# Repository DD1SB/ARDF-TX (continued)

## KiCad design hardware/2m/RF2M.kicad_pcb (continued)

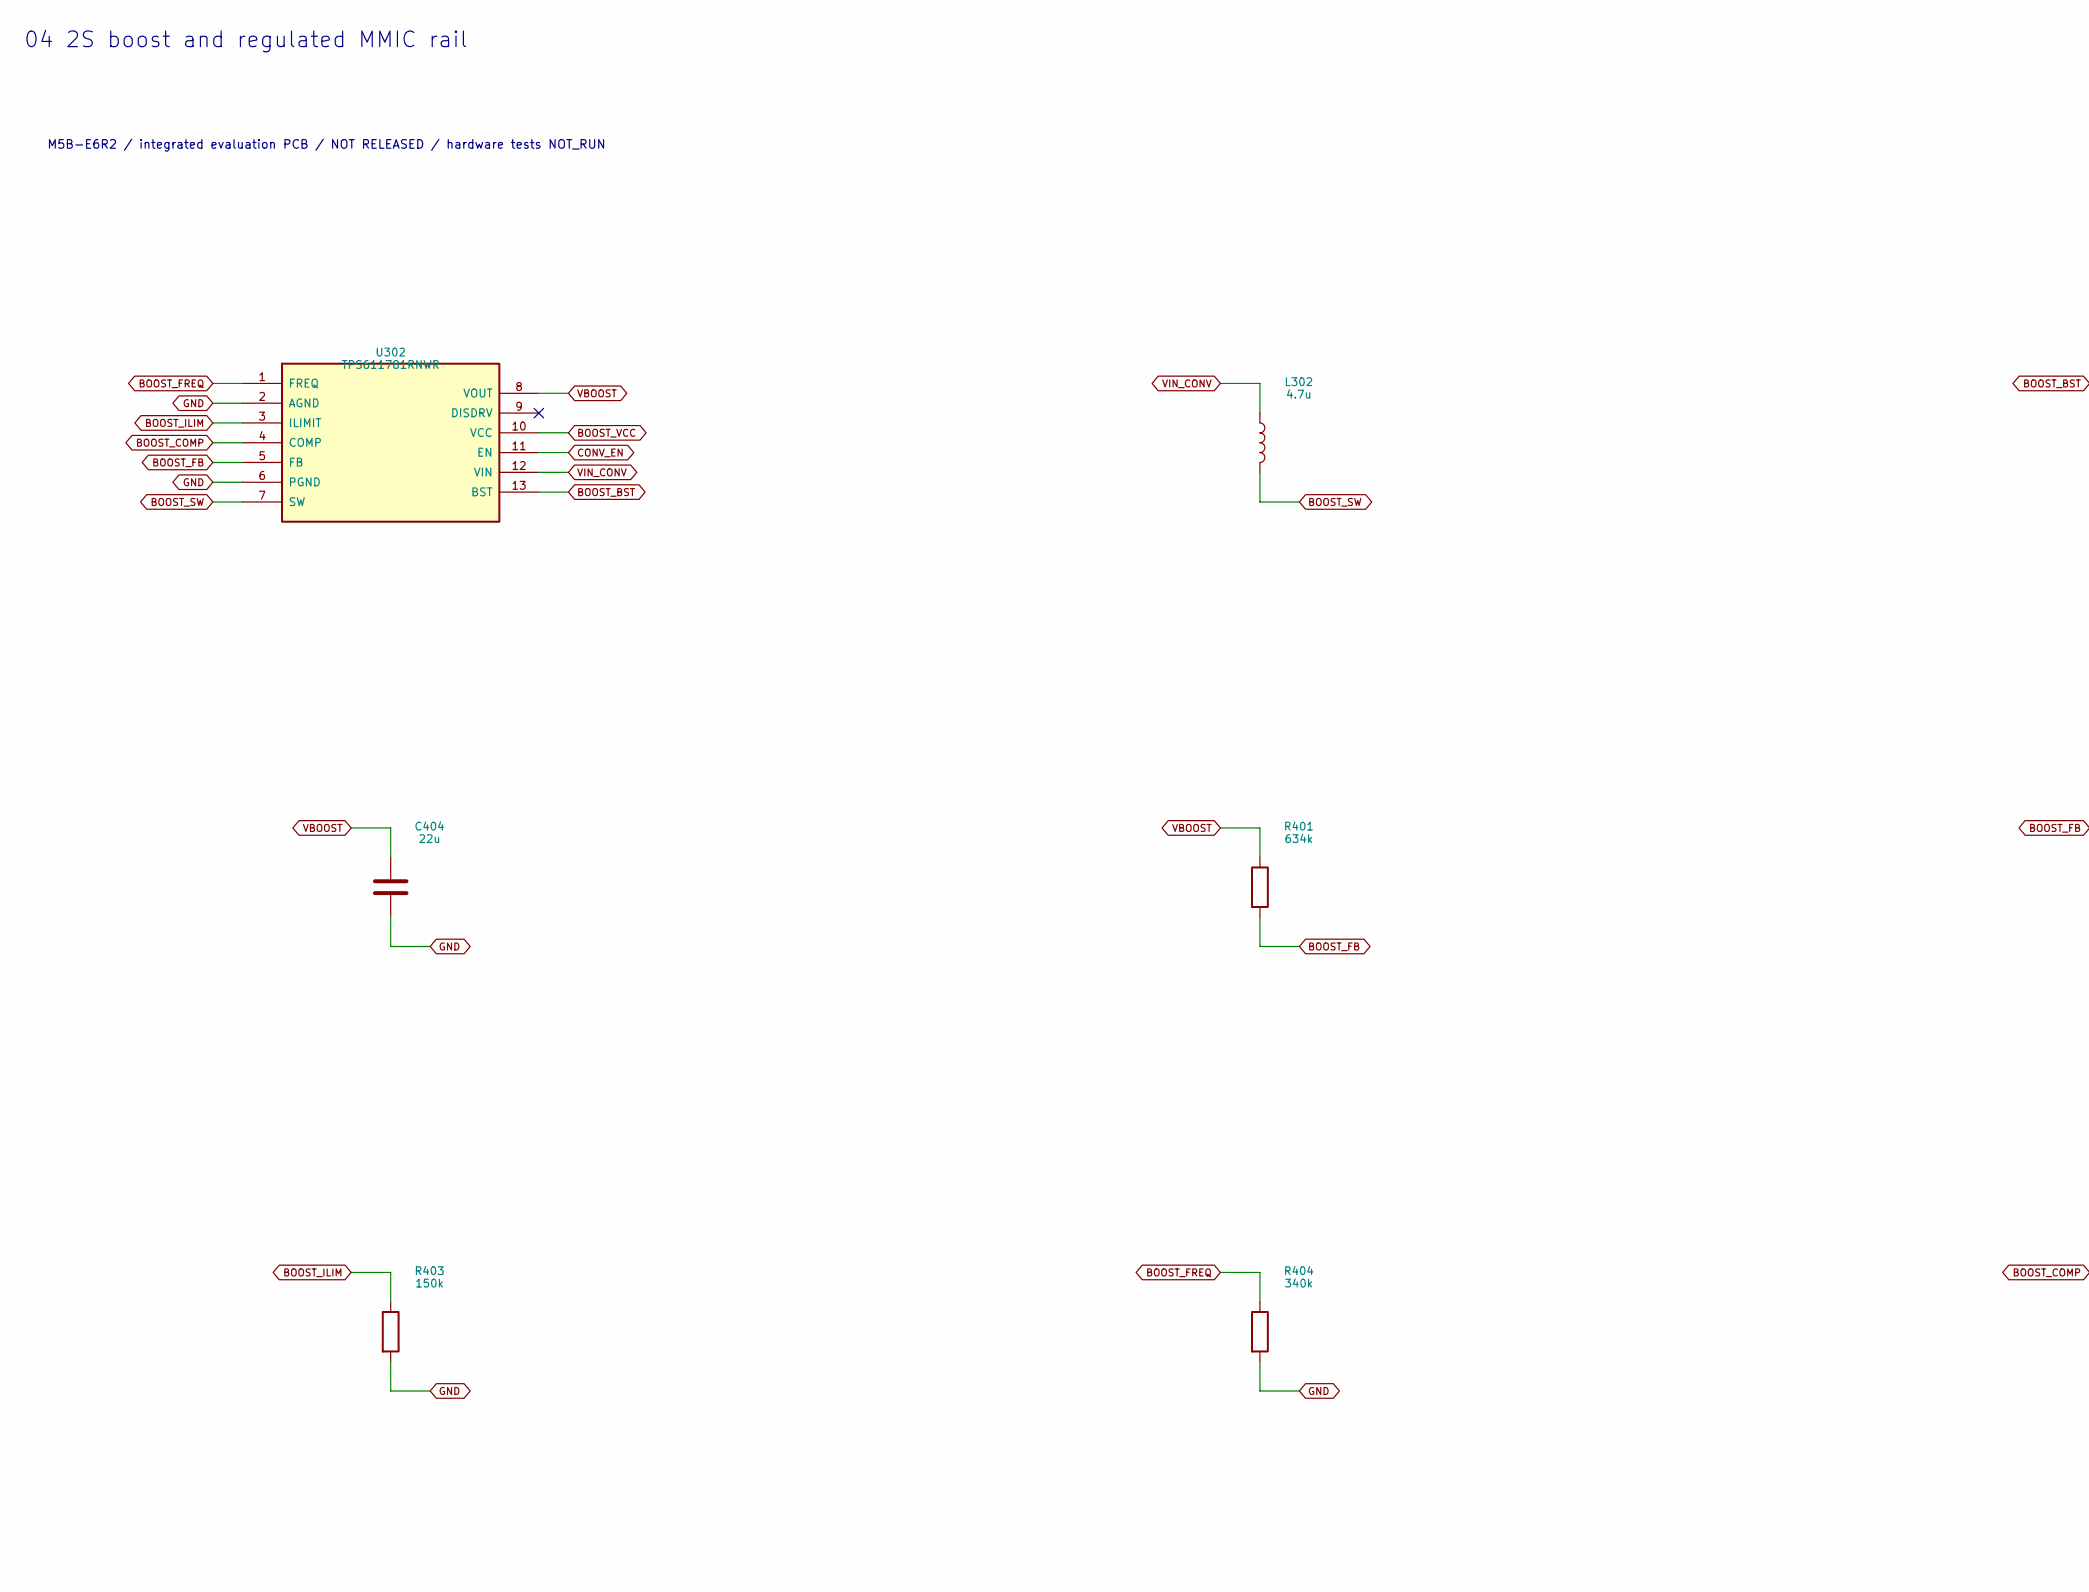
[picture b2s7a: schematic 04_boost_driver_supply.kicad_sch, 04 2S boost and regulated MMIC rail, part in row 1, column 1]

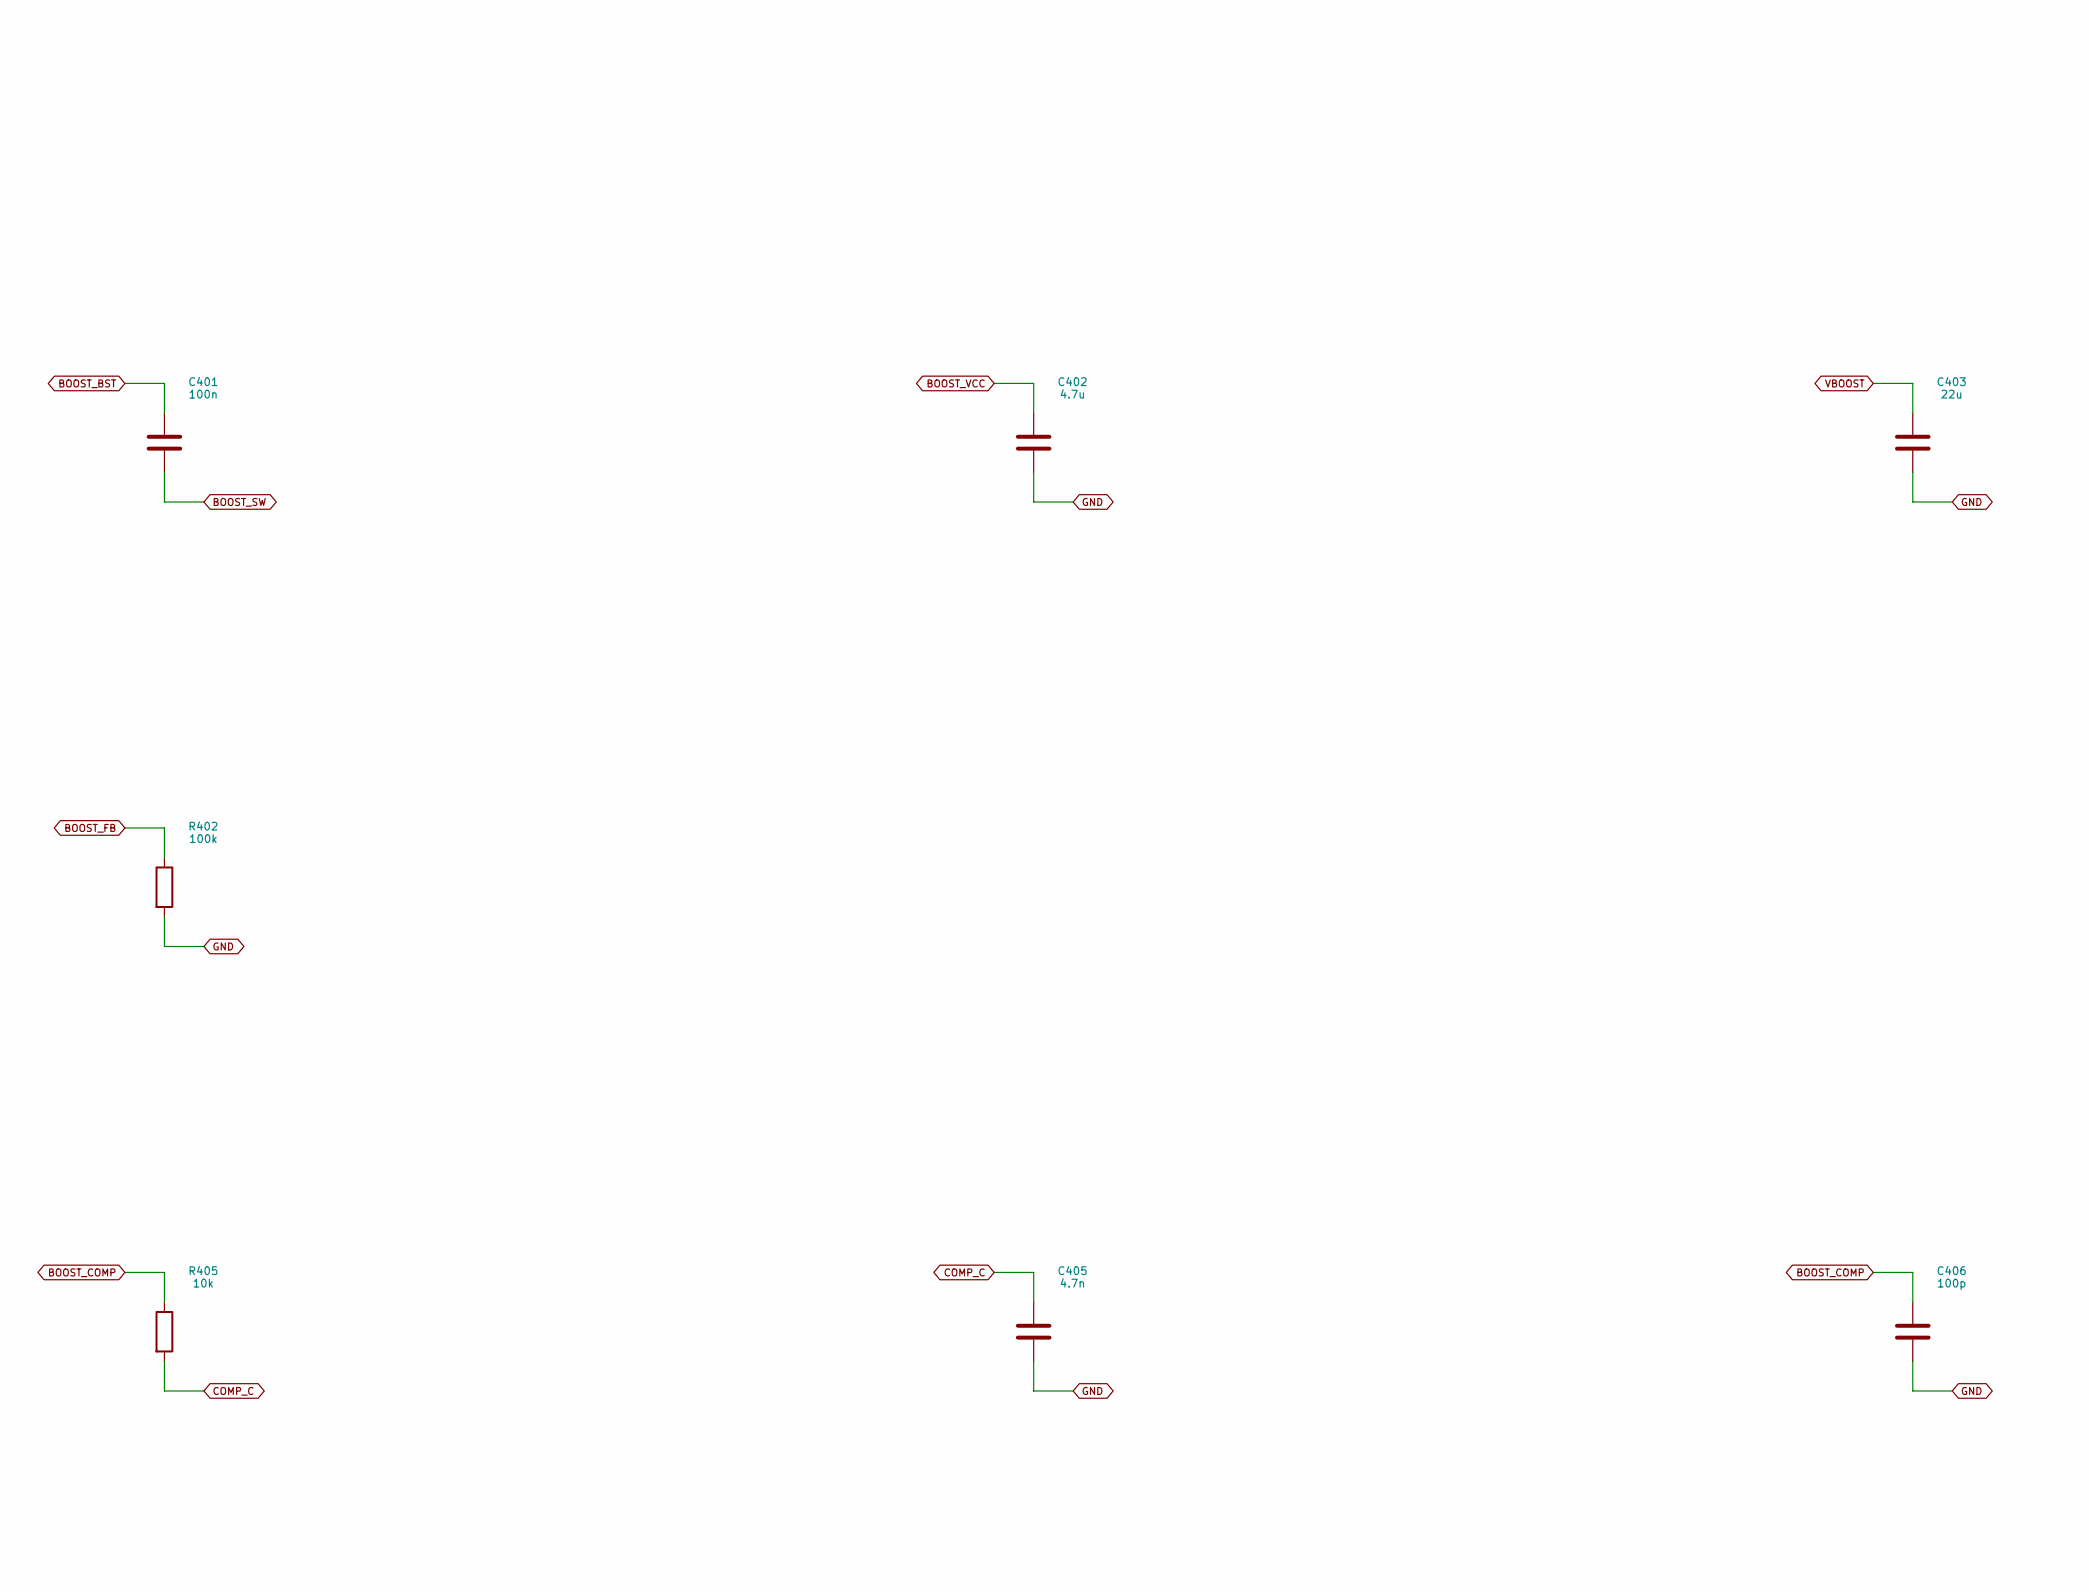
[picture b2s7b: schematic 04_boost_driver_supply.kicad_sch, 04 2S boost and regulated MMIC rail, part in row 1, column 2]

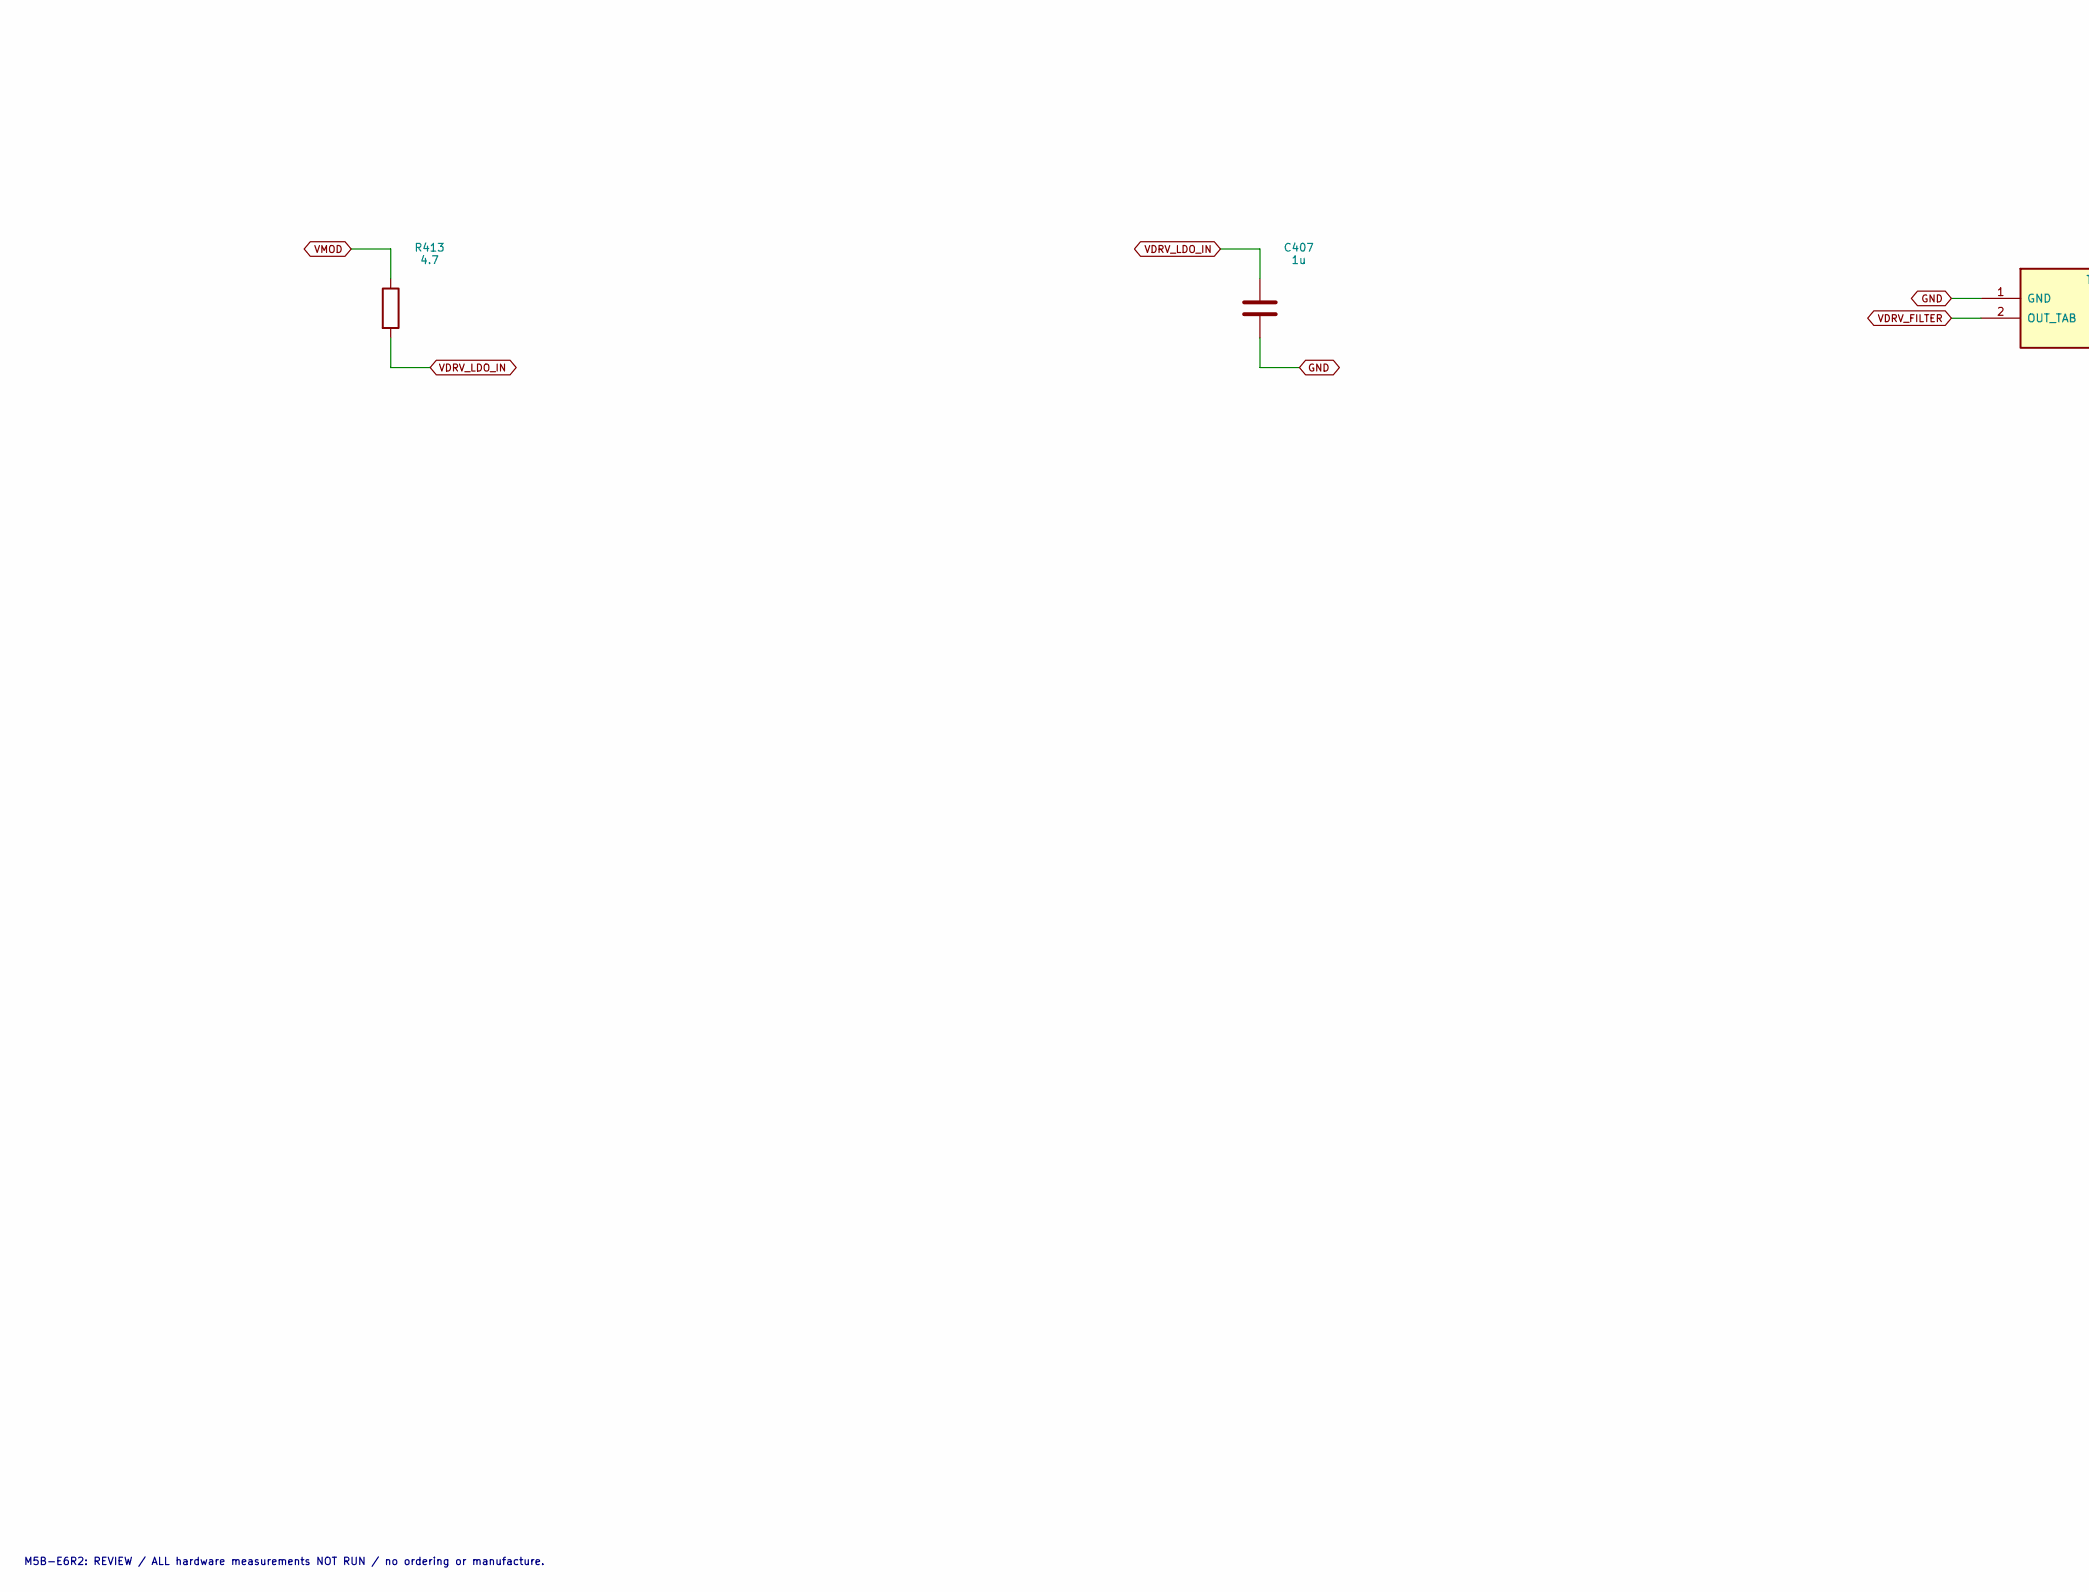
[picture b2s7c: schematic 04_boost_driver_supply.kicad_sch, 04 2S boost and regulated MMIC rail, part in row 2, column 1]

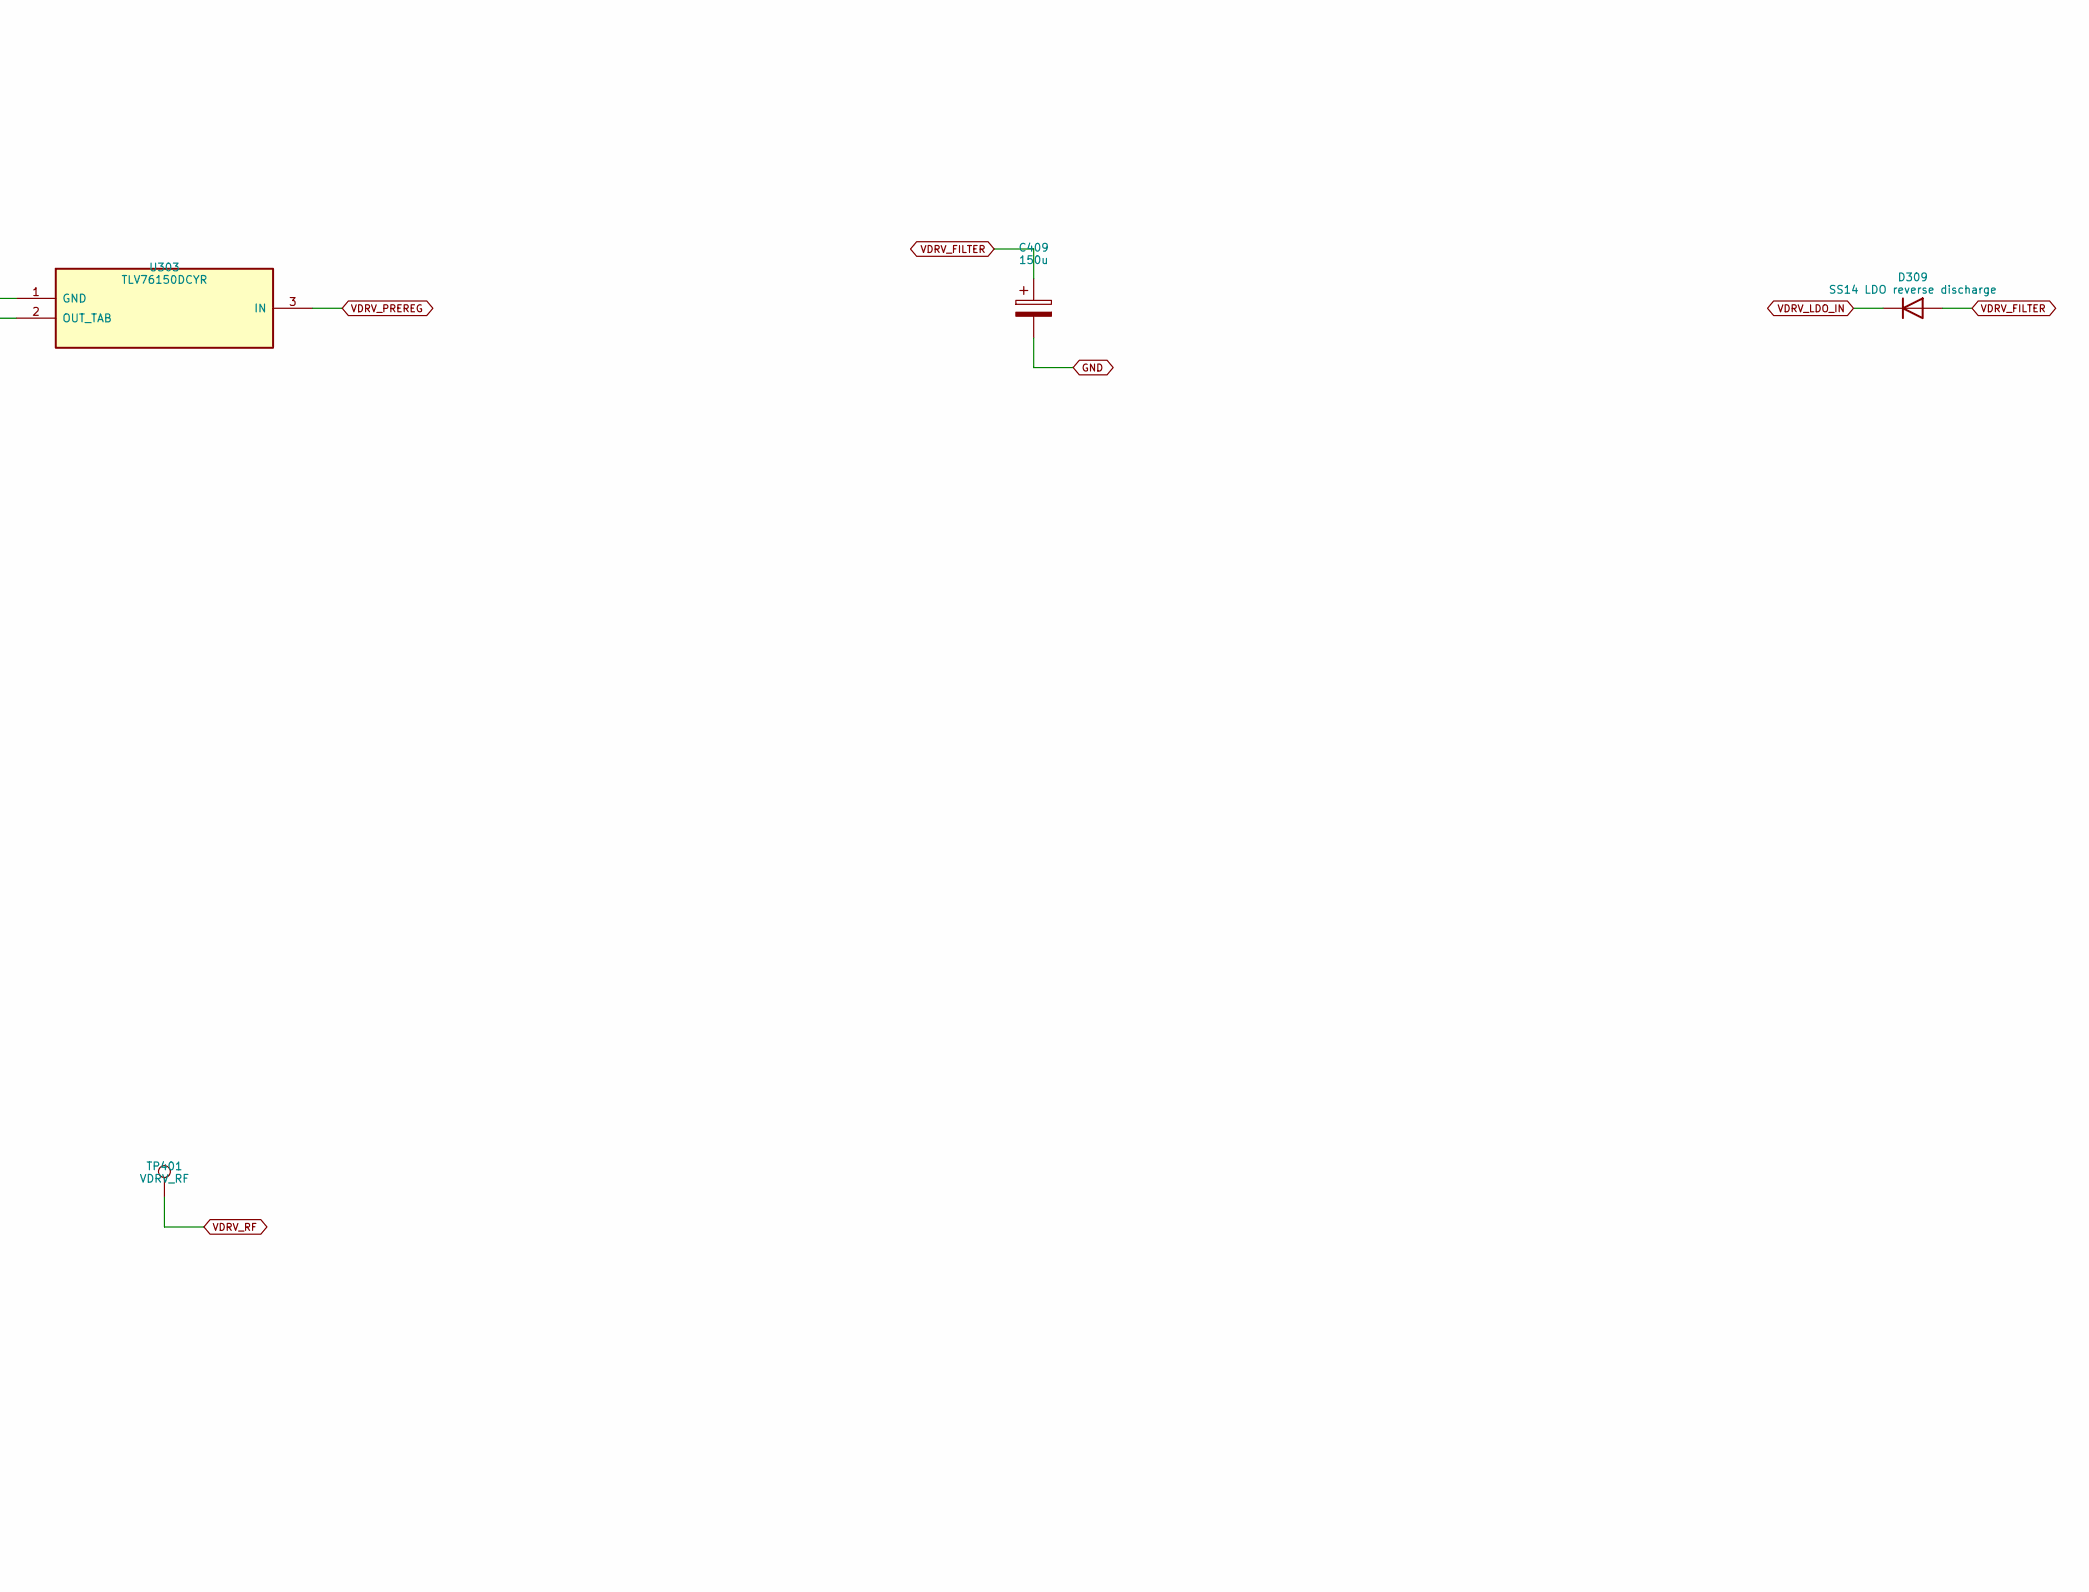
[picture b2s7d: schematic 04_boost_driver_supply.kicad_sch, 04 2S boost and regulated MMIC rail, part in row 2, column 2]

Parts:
C401: 100n; C_0603_1608Metric_E3; MPN CC0603KRX7R8BB104
C402: 4.7u; C_1206_3216Metric_E3; MPN GRM31CR71E475KA88L
C403, C404: 22u; C_1210_3225Metric_E3; MPN GRM32ER71E226KE15L
C405: 4.7n; C_0603_1608Metric_E3; MPN CC0603JRNPO9BN472
C406: 100p; C_0603_1608Metric_E3; MPN CC0603JRNPO9BN101
C407: 1u; C_0805_2012Metric_E3; MPN CC0805KKX7R9BB105
C409: 150u; CP_Panasonic_OSCON_C10; MPN 25SVPG150M
D309: SS14 LDO reverse discharge; D_SMA_E3; MPN SS14-E3/61T
L302: 4.7u; Bourns_SRP1265A; MPN SRP1265A-4R7M
R401: 634k; R_0603_1608Metric_E3; MPN RC0603FR-07634KL
R402: 100k; R_0603_1608Metric_E3; MPN RC0603FR-07100KL
R403: 150k; R_0603_1608Metric_E3; MPN RC0603FR-07150KL
R404: 340k; R_0603_1608Metric_E3; MPN RC0603FR-07340KL
R405: 10k; R_0603_1608Metric_E3; MPN RC0603FR-0710KL
R413: 4.7; R_2512_6332Metric_E3; MPN RC2512FK-074R7L
TP401: VDRV_RF; TestPoint_Pad_D1.0mm_E3; MPN PCB feature
U302: TPS611781RNWR; TI_RNW0013A_4222804C; MPN TPS611781RNWR
U303: TLV76150DCYR; SOT-223-3_TabPin2_E3; MPN TLV76150DCYR

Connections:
BOOST_BST: C401.1, U302.13 (BST)
BOOST_COMP: C406.1, R405.1, U302.4 (COMP)
BOOST_FB: R401.2, R402.1, U302.5 (FB)
BOOST_FREQ: R404.1, U302.1 (FREQ)
BOOST_ILIM: R403.1, U302.3 (ILIMIT)
BOOST_SW: C401.2, L302.2, U302.7 (SW)
BOOST_VCC: C402.1, U302.10 (VCC)
COMP_C: C405.1, R405.2
CONV_EN: U302.11 (EN); also elsewhere on the board
GND: C402.2, C403.2, C404.2, C405.2, C406.2, C407.2, C409.2, R402.2, R403.2, R404.2, U302.2 (AGND), U302.6 (PGND), U303.1 (GND); also elsewhere on the board
VBOOST: C403.1, C404.1, R401.1, U302.8 (VOUT); also elsewhere on the board
VDRV_FILTER: C409.1, D309.2 (A), U303.2 (OUT_TAB); also elsewhere on the board
VDRV_LDO_IN: C407.1, D309.1 (K), R413.2; also elsewhere on the board
VDRV_PREREG: U303.3 (IN); also elsewhere on the board
VDRV_RF: TP401.1; also elsewhere on the board
VIN_CONV: L302.1, U302.12 (VIN); also elsewhere on the board
VMOD: R413.1; also elsewhere on the board

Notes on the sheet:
04 2S boost and regulated MMIC rail
M5B-E6R2 / integrated evaluation PCB / NOT RELEASED / hardware tests NOT_RUN
M5B-E6R2: REVIEW / ALL hardware measurements NOT RUN / no ordering or manufacture.

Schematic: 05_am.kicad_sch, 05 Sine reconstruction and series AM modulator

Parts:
C501, C502, C503, C504, C505: 4.7n; C_0603_1608Metric_E3; MPN CC0603JRNPO9BN472
C506: 100n; C_0603_1608Metric_E3; MPN CC0603KRX7R8BB104
Q401: D45H11; TO220_Flat_CommonPlane_E6R2; MPN D45H11
Q402: BD139; TO126_Flat_CommonPlane_E6R2; MPN BD139
Q403, Q404, Q405: MMBT3904,215; SOT-23_E3; MPN MMBT3904,215
R501, R502, R503, R504, R509, R512: 10k; R_0603_1608Metric_E3; MPN RC0603FR-0710KL
R505: 4.7k; R_0603_1608Metric_E3; MPN RC0603FR-074K7L
R506: 10; R_2512_6332Metric_E3; MPN RC2512FK-0710RL
R507: 8.2; R_0805_2012Metric_E3; MPN RC0805FR-078R2L
R508, R516: 1k; R_0603_1608Metric_E3; MPN RC0603FR-071KL
R510: 100k; R_0603_1608Metric_E3; MPN RC0603FR-07100KL
R511: 18k; R_0603_1608Metric_E3; MPN RC0603FR-0718KL
R513: 1k; R_1206_3216Metric_E3; MPN RC1206FR-071KL
R514: 27k; R_0603_1608Metric_E3; MPN RC0603FR-0727KL
R517: 0; R_0603_1608Metric_E3; MPN RC0603JR-070RL; not fitted
R518: 100k; R_0603_1608Metric_E3; MPN RC0603FR-07100KL; not fitted
U401: TLV9004IDR; SOIC-14_3.9x8.7mm_P1.27mm_E3; MPN TLV9004IDR
U402: SN74LVC1G3157DBVR; SOT-23-6_E3; MPN SN74LVC1G3157DBVR

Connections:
AF_DC: C503.2, U401.6 (IN_B_N), U401.7 (OUT_B), U402.1 (B2_KEY1)
AF_F1: C503.1, R503.2, R504.1
AF_F2: C504.1, R504.2, U401.5 (IN_B_P)
AF_PWM: R503.1; also elsewhere on the board
AM_COMMAND: R514.1, R516.1, U402.4 (A_COMMON); also elsewhere on the board
GND: C502.2, C504.2, C506.2, Q403.2 (E), Q404.2 (E), Q405.2 (E), R507.2, R510.2, R512.2, R513.2, R518.2, U401.11 (VSS), U402.2 (GND), U402.3 (B1_KEY0); also elsewhere on the board
KEY: U402.6 (SELECT); also elsewhere on the board
LEVEL_DC: C501.2, U401.1 (OUT_A), U401.2 (IN_A_N)
LEVEL_F1: C501.1, R501.2, R502.1
LEVEL_F2: C502.1, R502.2, U401.3 (IN_A_P)
LEVEL_PWM: R501.1; also elsewhere on the board
LOCAL_MOD_OFF: R509.1; also elsewhere on the board
MOD_BASE: Q402.1 (B), Q403.3 (C), Q404.3 (C), R508.2, R510.1
MOD_COMMAND: Q405.3 (C), R516.2, R518.1, U401.10 (IN_C_P)
MOD_COMMAND_OFF_BASE: Q405.1 (B); also elsewhere on the board
MOD_DRIVE: C505.1, R508.1, R517.1, U401.8 (OUT_C)
MOD_E: Q402.3 (E), Q403.1 (B), R507.1; also elsewhere on the board
MOD_OFF_BASE: Q404.1 (B), R509.2
MOD_SINK: Q402.2 (C), R506.2
PASS_BASE: Q401.1 (B), R505.1, R506.1
TRAIN_BASE_DRIVE: U401.14 (OUT_D); also elsewhere on the board
TRAIN_COMMAND: R514.2, U401.12 (IN_D_P); also elsewhere on the board
TRAIN_EMITTER_DC: U401.13 (IN_D_N); also elsewhere on the board
V3V3: U401.4 (VDD), U402.5 (VCC); also elsewhere on the board
VMOD: Q401.3 (E), R505.2; also elsewhere on the board
VPA: C506.1, R511.1, R513.1; also elsewhere on the board
VPA_FB: C505.2, R511.2, R512.1, R517.2, U401.9 (IN_C_N)
VPA_PRE: Q401.2 (C); also elsewhere on the board

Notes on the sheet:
05 Sine reconstruction and series AM modulator
M5B-E6R2 / integrated evaluation PCB / NOT RELEASED / hardware tests NOT_RUN
M5B-E6R2: REVIEW / ALL hardware measurements NOT RUN / no ordering or manufacture.

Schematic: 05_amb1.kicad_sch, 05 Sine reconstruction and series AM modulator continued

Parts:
C507, C508: 100n; C_0603_1608Metric_E3; MPN CC0603KRX7R8BB104
R515: 10k; R_0603_1608Metric_E3; MPN RC0603FR-0710KL
TP501: AM_COMMAND; TestPoint_Pad_D1.0mm_E3; MPN PCB feature
TP502: VPA; TestPoint_Pad_D1.0mm_E3; MPN PCB feature
TP503: MOD_E; TestPoint_Pad_D1.0mm_E3; MPN PCB feature

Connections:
AM_COMMAND: TP501.1; also elsewhere on the board
GND: C507.2, C508.2, R515.2; also elsewhere on the board
MOD_E: TP503.1; also elsewhere on the board
TRAIN_COMMAND: R515.1; also elsewhere on the board
V3V3: C507.1, C508.1; also elsewhere on the board
VPA: TP502.1; also elsewhere on the board

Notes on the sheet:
05 Sine reconstruction and series AM modulator continued
M5B-E6R2 / integrated evaluation PCB / NOT RELEASED / hardware tests NOT_RUN
M5B-E6R2: REVIEW / ALL hardware measurements NOT RUN / no ordering or manufacture.

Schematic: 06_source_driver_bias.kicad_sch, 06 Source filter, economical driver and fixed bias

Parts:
C601: 100p; C_0603_1608Metric_E3; MPN CC0603JRNPO9BN101
C602, C604, C615: 1n; C_0603_1608Metric_E3; MPN CC0603JRNPO9BN102
C603, C607: 100n; C_0603_1608Metric_E3; MPN CC0603KRX7R8BB104
C611, C614: 8.2p; C_0603_1608Metric_E3; MPN CC0603CRNPO9BN8R2
C612, C613: 33p; C_0603_1608Metric_E3; MPN CC0603JRNPO9BN330
D501: 6.2V bias ceiling; D_SOD-123F_E3; MPN BZT52H-C6V2,115
L604: 150n; Coilcraft_1812SMS_Doc184; MPN 1812SMS-R15JLC
L606: 33n; Coilcraft_1812SMS_Doc184; MPN 1812SMS-33NJLC
L611, L613: 56n; L_0603_1608Metric_E3; MPN LQW18AN56NG80D
L612: 91n; L_0603_1608Metric_E3; MPN LQW18AN91NG80D
Q501: PD54008L-E; PD54008L_ST_GDS_5x5; MPN PD54008L-E
Q502: 2N7002; SOT-23_E3; MPN 2N7002,215
R602: 71.5; R_0603_1608Metric_E3; MPN RC0603FR-0771R5L
R603, R604: 96.5; R_0603_1608Metric_E3; MPN RC0603FR-0796R5L
R606: 1k; R_0603_1608Metric_E3; MPN RC0603FR-071KL
RV501: 10k bias trim; Potentiometer_Bourns_3296W_Vertical_E3; MPN 3296W-1-103LF
TP601: PA_GATE; Probe_Pad_0p6; MPN PCB feature
U501: PHA-1+; PHA1_DF782_RevG; MPN PHA-1+

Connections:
61A: C612.1, L611.2, L612.1
61B: C613.1, L612.2, L613.1
BIAS_TOP: D501.1 (K), R606.2, RV501.1
BIAS_WIPER: C607.1, L606.1, Q502.3 (D), RV501.2
DRIVER_IN: C615.2, U501.1 (RF_IN)
DRIVER_PAD: C615.1, R602.2, R604.1
GND: C603.2, C604.2, C607.2, C611.2, C612.2, C613.2, C614.2, D501.2 (A), Q501.S, Q502.2 (S), R603.2, R604.2, RV501.3, U501.2 (GND_LEAD), U501.4 (GROUND_PADDLE); also elsewhere on the board
MMIC_COUPLED: C602.2; also elsewhere on the board
MMIC_RF_DC: C602.1, L604.2, U501.3 (RF_OUT_DC5V)
NORMAL_CLOCK_BUF: C601.1; also elsewhere on the board
NORMAL_OFF: Q502.1 (G); also elsewhere on the board
PA_DRAIN: Q501.D; also elsewhere on the board
PA_GATE: L606.2, Q501.G, TP601.1; also elsewhere on the board
SRC_FILT: C614.1, L613.2, R602.1, R603.1
SRC_RF: C601.2, C611.1, L611.1
VDRV_MMIC: C603.1, C604.1, L604.1; also elsewhere on the board
VMOD: R606.1; also elsewhere on the board

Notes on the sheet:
06 Source filter, economical driver and fixed bias
M5B-E6R2 / integrated evaluation PCB / NOT RELEASED / hardware tests NOT_RUN
M5B-E6R2: REVIEW / ALL hardware measurements NOT RUN / no ordering or manufacture.

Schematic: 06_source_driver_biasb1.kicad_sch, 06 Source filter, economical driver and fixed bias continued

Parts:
J501: NORMAL 50ohm SMA; SMA_Amphenol_132134_Vertical_E3; MPN 132134
TP602: PA_DRAIN; Probe_Pad_0p6; MPN PCB feature
TP603: ST_LPF_IN; Probe_Pad_0p6; MPN PCB feature
TP604: MMIC_AC; Probe_Pad_0p6; MPN PCB feature

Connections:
GND: J501.2 (Ext); also elsewhere on the board
MMIC_AC: TP604.1; also elsewhere on the board
NORMAL_RF: J501.1 (In); also elsewhere on the board
PA_DRAIN: TP602.1; also elsewhere on the board
ST_LPF_IN: TP603.1; also elsewhere on the board

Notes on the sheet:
06 Source filter, economical driver and fixed bias continued
M5B-E6R2 / integrated evaluation PCB / NOT RELEASED / hardware tests NOT_RUN
M5B-E6R2: REVIEW / ALL hardware measurements NOT RUN / no ordering or manufacture.

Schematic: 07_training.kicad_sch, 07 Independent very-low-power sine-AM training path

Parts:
C701, C702, C704: 100p; C_0603_1608Metric_E3; MPN CC0603JRNPO9BN101
C703, C705, C706: 1n; C_0603_1608Metric_E3; MPN CC0603JRNPO9BN102
C711, C714: 8.2p; C_0603_1608Metric_E3; MPN CC0603CRNPO9BN8R2
C712, C713: 33p; C_0603_1608Metric_E3; MPN CC0603JRNPO9BN330
L704: 180n; L_0603_1608Metric_E3; MPN LQW18ANR18G80D
L711, L713: 56n; L_0603_1608Metric_E3; MPN LQW18AN56NG80D
L712: 91n; L_0603_1608Metric_E3; MPN LQW18AN91NG80D
Q701: MMBTH10LT1G; SOT-23_E3; MPN MMBTH10LT1G
Q702, Q703, Q704: MMBT3904,215; SOT-23_E3; MPN MMBT3904,215
R702: 680; R_0603_1608Metric_E3; MPN RC0603FR-07680RL
R703: 10; R_0603_1608Metric_E3; MPN RC0603FR-0710RL
R704: 100; R_1206_3216Metric_E3; MPN RC1206FR-07100RL
R705: 47; R_0603_1608Metric_E3; MPN RC0603FR-0747RL
R706, R708: 10k; R_0603_1608Metric_E3; MPN RC0603FR-0710KL
R707, R709: 1k; R_0603_1608Metric_E3; MPN RC0603FR-071KL
R710: 4.7k; R_0603_1608Metric_E3; MPN RC0603FR-074K7L
R714: 100; R_0603_1608Metric_E3; MPN RC0603FR-07100RL
R715: 51.1; R_0603_1608Metric_E3; MPN RC0603FR-0751R1L
U701: SN74LVC1G125DBVR; SOT-23-5_E3; MPN SN74LVC1G125DBVR

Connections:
71A: C712.1, L711.2, L712.1
71B: C713.1, L712.2, L713.1
CLK_TRAIN: U701.2 (A); also elsewhere on the board
GND: C703.2, C704.2, C705.2, C711.2, C712.2, C713.2, C714.2, Q702.2 (E), Q703.2 (E), Q704.2 (E), R703.2, R705.2, R715.2, U701.3 (GND); also elsewhere on the board
TRAIN_BASE: C702.2, L704.2, Q701.1 (B), Q702.3 (C)
TRAIN_BASE_DRIVE: R706.1; also elsewhere on the board
TRAIN_BASE_RF: C702.1, R702.2, R703.1
TRAIN_BIAS: C704.1, L704.1, R706.2
TRAIN_CLOCK_BUF: R714.1, U701.4 (Y)
TRAIN_CLOCK_LIMIT: C701.1, R714.2
TRAIN_COLLECTOR: C706.1, Q701.3 (C), R704.2
TRAIN_COMMAND: Q704.3 (C); also elsewhere on the board
TRAIN_EMITTER: C703.1, Q701.2 (E), R705.1, R707.1
TRAIN_EMITTER_DC: C705.1, R707.2; also elsewhere on the board
TRAIN_FILT: C714.1, L713.2, R702.1, R715.1
TRAIN_INVERT_BASE: Q703.1 (B), R710.2
TRAIN_OFF: Q703.3 (C), R708.1, R709.1, U701.1 (OE_N)
TRAIN_OFF_BASE: Q702.1 (B), Q704.1 (B), R708.2
TRAIN_OUT_RAW: C706.2; also elsewhere on the board
TRAIN_PERMIT: R710.1; also elsewhere on the board
TRAIN_SRC: C701.2, C711.1, L711.1
V3V3: R704.1, R709.2, U701.5 (VCC); also elsewhere on the board

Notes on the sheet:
07 Independent very-low-power sine-AM training path
M5B-E6R2 / integrated evaluation PCB / NOT RELEASED / hardware tests NOT_RUN
M5B-E6R2: REVIEW / ALL hardware measurements NOT RUN / no ordering or manufacture.

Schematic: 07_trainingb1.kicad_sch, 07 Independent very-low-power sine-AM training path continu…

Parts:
C721, C724: 8.2p; C_0603_1608Metric_E3; MPN CC0603CRNPO9BN8R2
C722, C723: 33p; C_0603_1608Metric_E3; MPN CC0603JRNPO9BN330
J701: TRAIN MMCX 50ohm; WR-MMCX_Wuerth_66012102111404_Vertical_E3; MPN 66012102111404
L721, L723: 56n; L_0603_1608Metric_E3; MPN LQW18AN56NG80D
L722: 91n; L_0603_1608Metric_E3; MPN LQW18AN91NG80D
R711: 154; R_0603_1608Metric_E3; MPN RC0603FR-07154RL
R712, R713: 68.1; R_0603_1608Metric_E3; MPN RC0603FR-0768R1L
TP701: TRAIN_OUT_RAW; TestPoint_Pad_D1.0mm_E3; MPN PCB feature
TP702: TRAIN_RF; TestPoint_Pad_D1.0mm_E3; MPN PCB feature

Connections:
72A: C722.1, L721.2, L722.1
72B: C723.1, L722.2, L723.1
GND: C721.2, C722.2, C723.2, C724.2, J701.2 (Ext), R712.2, R713.2; also elsewhere on the board
TRAIN_OUT_FILT: C724.1, L723.2, R711.1, R712.1
TRAIN_OUT_RAW: C721.1, L721.1, TP701.1; also elsewhere on the board
TRAIN_RF: J701.1 (In), R711.2, R713.1, TP702.1

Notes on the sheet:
07 Independent very-low-power sine-AM training path continued
M5B-E6R2 / integrated evaluation PCB / NOT RELEASED / hardware tests NOT_RUN
M5B-E6R2: REVIEW / ALL hardware measurements NOT RUN / no ordering or manufacture.

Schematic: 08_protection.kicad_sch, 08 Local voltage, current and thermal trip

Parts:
R801: 150; R_0603_1608Metric_E3; MPN RC0603FR-07150RL
R802: 620; R_0603_1608Metric_E3; MPN RC0603FR-07620RL
R803: 470; R_0603_1608Metric_E3; MPN RC0603FR-07470RL
R804, R806, R808, R810, R812, R814, R820, R822, R823, R825, R827: 10k; R_0603_1608Metric_E3; MPN RC0603FR-0710KL
R805: 160k; R_0603_1608Metric_E3; MPN RC0603FR-07160KL
R807: 58.3k; R_0603_1608Metric_E3; MPN RC0603FR-0758K3L
R809: 39.2k; R_0603_1608Metric_E3; MPN RC0603FR-0739K2L
R811: 120k; R_0603_1608Metric_E3; MPN RC0603FR-07120KL
R813: 20.9k; R_0603_1608Metric_E3; MPN RC0603FR-0720K9L
R815: 73.2k; R_0603_1608Metric_E3; MPN RT0603BRD0773K2L
R816, R818: 10k; R_0603_1608Metric_E3; MPN RT0603BRD0710KL
R817: 29.4k; R_0603_1608Metric_E3; MPN RT0603BRD0729K4L
R819: 110k; R_0603_1608Metric_E3; MPN RC0603FR-07110KL
R821: 26.5k; R_0603_1608Metric_E3; MPN RC0603FR-0726K5L
R824: 49.9k; R_0603_1608Metric_E3; MPN RC0603FR-0749K9L
R826: 1k; R_0603_1608Metric_E3; MPN RC0603FR-071KL
TH801: 10k NTC B3977; NTC_Remote_2Wire; MPN NTCLE100E3103JB0
U801: TL431BIDBZR; SOT-23_E3; MPN TL431BIDBZR
U804: INA180A1IDBVR; SOT-23-5_E3; MPN INA180A1IDBVR

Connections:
DRV_OV_REF: R817.2, R818.1; also elsewhere on the board
DRV_S: R815.2, R816.1; also elsewhere on the board
GND: R803.2, R806.2, R808.2, R810.2, R812.2, R814.2, R816.2, R818.2, R820.2, R822.2, R825.2, R827.2, TH801.2, U801.3 (A), U804.2 (GND); also elsewhere on the board
ISENSE: U804.1; also elsewhere on the board
OV_REF: R809.2, R810.1; also elsewhere on the board
POWER_FAULT_N: R804.1; also elsewhere on the board
REG_OV_REF: R813.2, R814.1; also elsewhere on the board
TEMP_HIGH: R826.2, R827.1; also elsewhere on the board
TEMP_LOW: R824.2, R825.1; also elsewhere on the board
TEMP_S: R823.2, TH801.1; also elsewhere on the board
UV_REF: R807.2, R808.1; also elsewhere on the board
V3V3: R801.1, R804.2, U804.5 (V+); also elsewhere on the board
VBAT_S: R805.2, R806.1; also elsewhere on the board
VDRV_FILTER: R815.1; also elsewhere on the board
VIN_PROT: R805.1; also elsewhere on the board
VMOD: U804.4 (-); also elsewhere on the board
VPA: R819.1; also elsewhere on the board
VPA_OV_REF: R821.2, R822.1; also elsewhere on the board
VPA_S: R819.2, R820.1; also elsewhere on the board
VREF1V0: R802.2, R803.1, R823.1, R824.1, R826.1; also elsewhere on the board
VREF2V5: R801.2, R802.1, R807.1, R809.1, R813.1, R817.1, R821.1, U801.1 (K), U801.2 (REF)
VREG_RAW: R811.1; also elsewhere on the board
VREG_S: R811.2, R812.1; also elsewhere on the board
VREG_SWITCH: U804.3 (+); also elsewhere on the board

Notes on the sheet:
08 Local voltage, current and thermal trip
M5B-E6R2 / integrated evaluation PCB / NOT RELEASED / hardware tests NOT_RUN
M5B-E6R2: REVIEW / ALL hardware measurements NOT RUN / no ordering or manufacture.
